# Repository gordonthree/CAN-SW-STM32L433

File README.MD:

# DC Power Distribution Module Controller
Compact controller board intended to interface with as many as four smart switch modules. Analog inputs for current and voltage sensing allow the controller to interrupt a load in place of a mechanical fuse or circuit breaker. An isolated CAN-FD interface provides expansion capability with other boards, displays and sensors.

# Control Node
* STM32L433 Microcontroller
* 3-pin terminal block for CANBUS connection with drain
* Pin-header connections for Profet Smart Switch modules
* Analog inputs for voltage and current sensing
* Jumper selected CAN terminator resistor
* LED indicator for 3.3v power
* LED indicator for status, controlled by the micro
* Bidirectional transient voltage protection diode for harsh environments
* Debugging header for UART1 serial port as well as SWLINK programming

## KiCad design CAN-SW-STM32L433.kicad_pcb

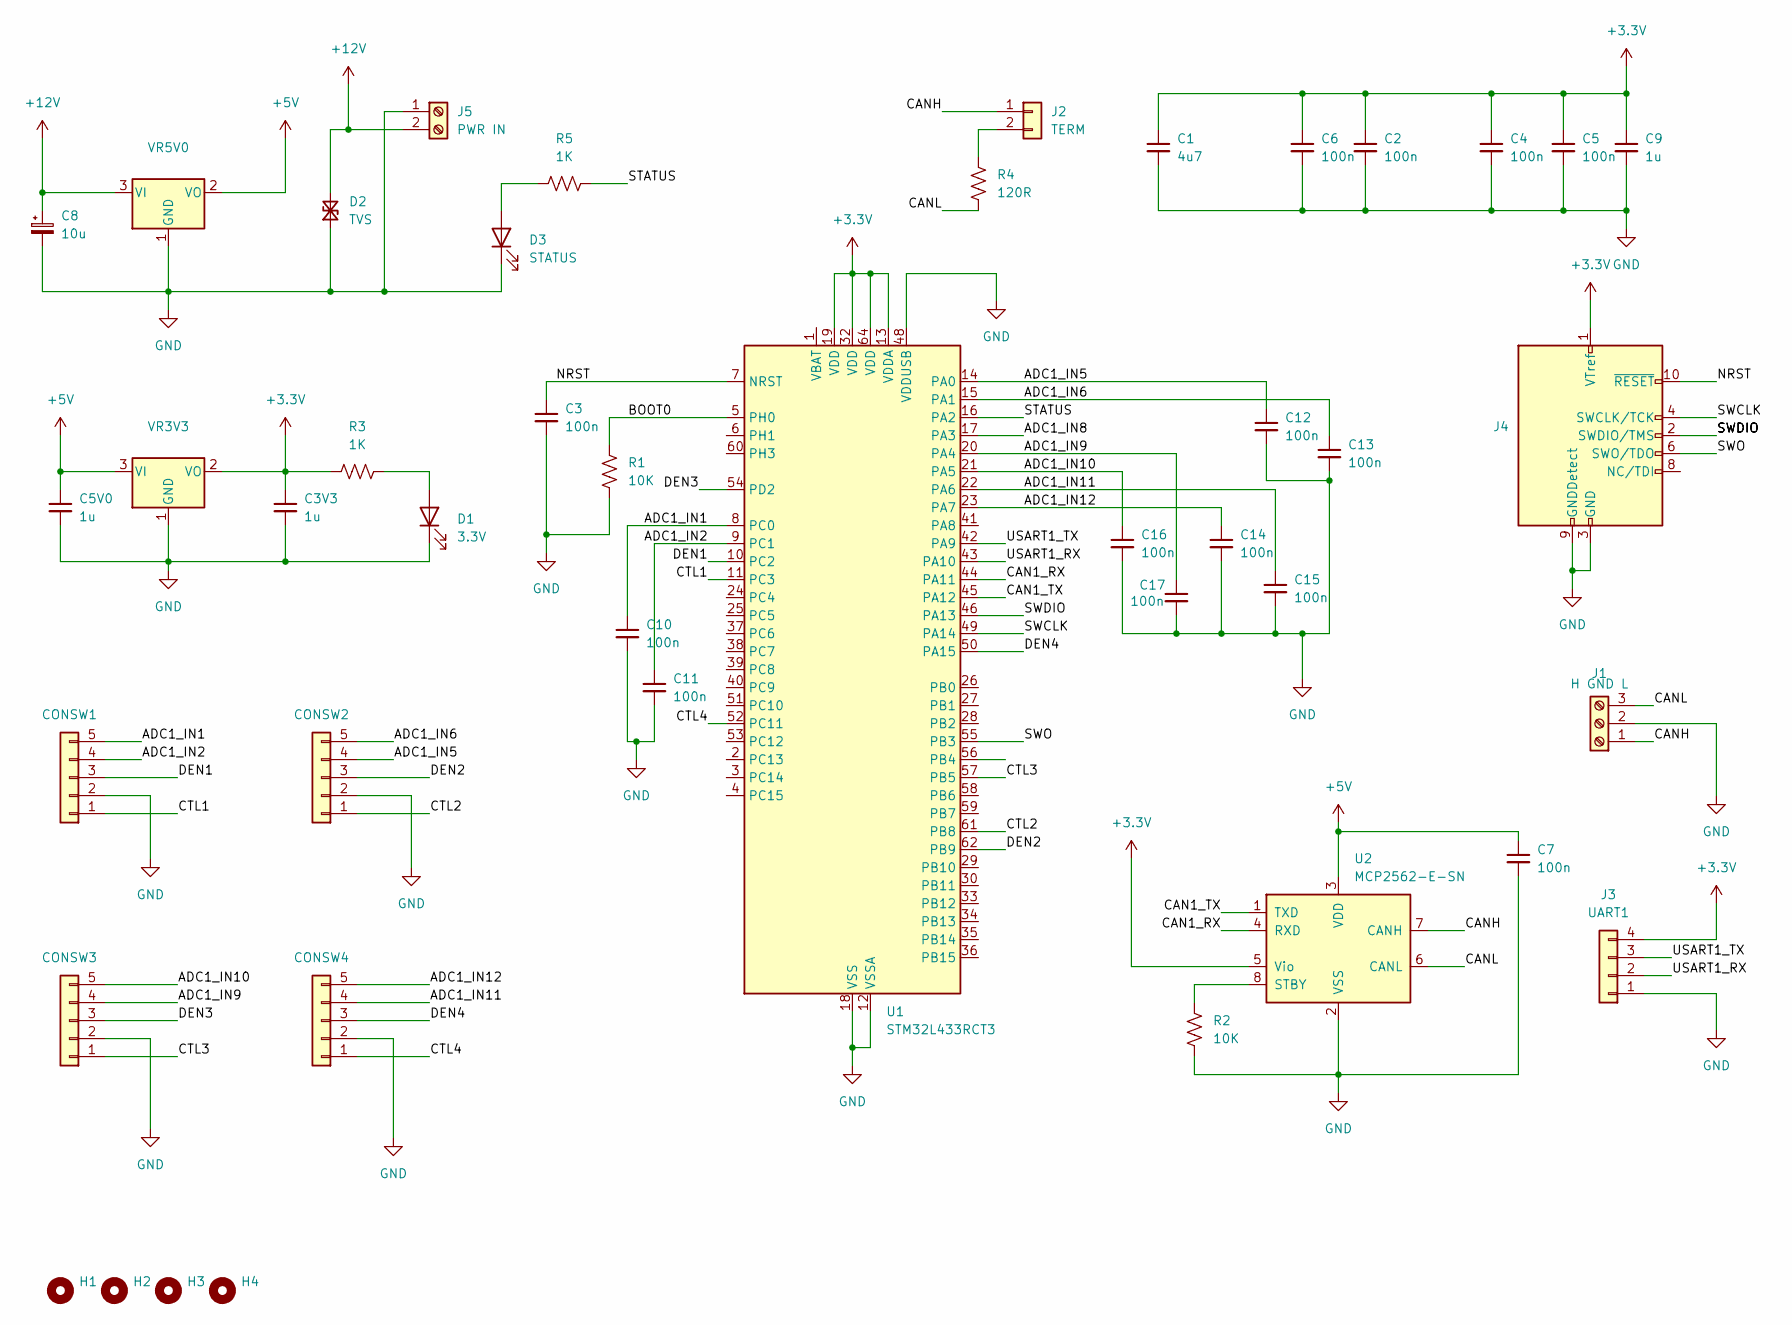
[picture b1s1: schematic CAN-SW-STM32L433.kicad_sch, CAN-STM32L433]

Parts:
C1: 4u7; C_0805_2012Metric_Pad1.18x1.45mm_HandSolder
C2, C3, C4, C5, C6, C7, C10, C11, C12, C13, C14, C15, C16, C17: 100n; C_0603_1608Metric_Pad1.08x0.95mm_HandSolder
C3V3, C5V0: 1u; C_0805_2012Metric_Pad1.18x1.45mm_HandSolder
C8: 10u; CP_Radial_D5.0mm_P2.50mm
C9: 1u; C_0603_1608Metric_Pad1.08x0.95mm_HandSolder
CONSW1, CONSW2, CONSW3, CONSW4: Conn_01x05; PinHeader_1x05_P2.54mm_Horizontal
D1: 3.3V; LED_D5.0mm_Clear
D2: TVS; D_SMA_Handsoldering
D3: STATUS; LED_D5.0mm_Clear
H1, H2, H3, H4: MountingHole; MountingHole_3.2mm_M3_DIN965
J1: H GND L; TerminalBlock_Phoenix_MKDS-1,5-3_1x03_P5.00mm_Horizontal
J2: TERM; PinHeader_1x02_P2.54mm_Vertical
J3: UART1; PinHeader_1x04_P2.54mm_Horizontal
J4: SWLINK; PinHeader_2x05_P2.54mm_Horizontal
J5: PWR IN; TerminalBlock_Phoenix_MKDS-1,5-2_1x02_P5.00mm_Horizontal
R1, R2: 10K; R_0603_1608Metric_Pad0.98x0.95mm_HandSolder
R3, R5: 1K; R_0603_1608Metric_Pad0.98x0.95mm_HandSolder
R4: 120R; R_Axial_DIN0207_L6.3mm_D2.5mm_P7.62mm_Horizontal
U1: STM32L433RCT3; LQFP-64_10x10mm_P0.5mm
U2: MCP2562-E-SN; SOIC-8_3.9x4.9mm_P1.27mm
VR3V3: TLV1117-33; SOT-223-3_TabPin2
VR5V0: TLV1117-50; SOT-223-3_TabPin2

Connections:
+3.3V: C1.1, C2.1, C3V3.1, C4.1, C5.1, C6.1, C9.1, J3.4, J4.1 (VTref), R3.1, U1.13 (VDDA), U1.19 (VDD), U1.32 (VDD), U1.64 (VDD), U2.5 (Vio), VR3V3.2 (VO)
+5V: C5V0.1, C7.1, U2.3 (VDD), VR3V3.3 (VI), VR5V0.2 (VO)
+12V: C8.1, D2.2 (A2), J5.2, VR5V0.3 (VI)
/ADC1_IN1: C10.1, CONSW1.5, U1.8 (PC0)
/ADC1_IN2: C11.1, CONSW1.4, U1.9 (PC1)
/ADC1_IN5: C12.1, CONSW2.4, U1.14 (PA0)
/ADC1_IN6: C13.1, CONSW2.5, U1.15 (PA1)
/ADC1_IN8: U1.17 (PA3)
/ADC1_IN9: C17.1, CONSW3.4, U1.20 (PA4)
/ADC1_IN10: C16.1, CONSW3.5, U1.21 (PA5)
/ADC1_IN11: C15.1, CONSW4.4, U1.22 (PA6)
/ADC1_IN12: C14.1, CONSW4.5, U1.23 (PA7)
/BOOT0: R1.1, U1.5 (PH0)
/CAN1_RX: U1.44 (PA11), U2.4 (RXD)
/CAN1_TX: U1.45 (PA12), U2.1 (TXD)
/CANH: J1.1, J2.1, U2.7 (CANH)
/CANL: J1.3, R4.2, U2.6 (CANL)
/CTL1: CONSW1.1, U1.11 (PC3)
/CTL2: CONSW2.1, U1.61 (PB8)
/CTL3: CONSW3.1, U1.57 (PB5)
/CTL4: CONSW4.1, U1.52 (PC11)
/DEN1: CONSW1.3, U1.10 (PC2)
/DEN2: CONSW2.3, U1.62 (PB9)
/DEN3: CONSW3.3, U1.54 (PD2)
/DEN4: CONSW4.3, U1.50 (PA15)
/NRST: C3.1, J4.10 (~RESET), U1.7 (NRST)
/STATUS: R5.2, U1.16 (PA2)
/SWCLK: J4.4 (SWCLK/TCK), U1.49 (PA14)
/SWDIO: J4.2 (SWDIO/TMS), U1.46 (PA13)
/SWO: J4.6 (SWO/TDO), U1.55 (PB3)
/USART1_RX: J3.2, U1.43 (PA10)
/USART1_TX: J3.3, U1.42 (PA9)
GND: C1.2, C2.2, C3.2, C3V3.2, C4.2, C5.2, C5V0.2, C6.2, C7.2, C8.2, C9.2, C10.2, C11.2, C12.2, C13.2, C14.2, C15.2, C16.2, C17.2, CONSW1.2, CONSW2.2, CONSW3.2, CONSW4.2, D1.1 (K), D2.1 (A1), D3.1 (K), J1.2, J3.1, J4.3 (GND), J4.5 (GND), J4.9 (GNDDetect), J5.1, R1.2, R2.2, U1.12 (VSSA), U1.18 (VSS), U1.31 (VSS), U1.47 (VSS), U1.48 (VDDUSB), U1.63 (VSS), U2.2 (VSS), VR3V3.1 (GND), VR5V0.1 (GND)
unnamed: D1.2 (A), R3.2
unnamed: D3.2 (A), R5.1
unnamed: J2.2, R4.1
unnamed: R2.1, U2.8 (STBY)

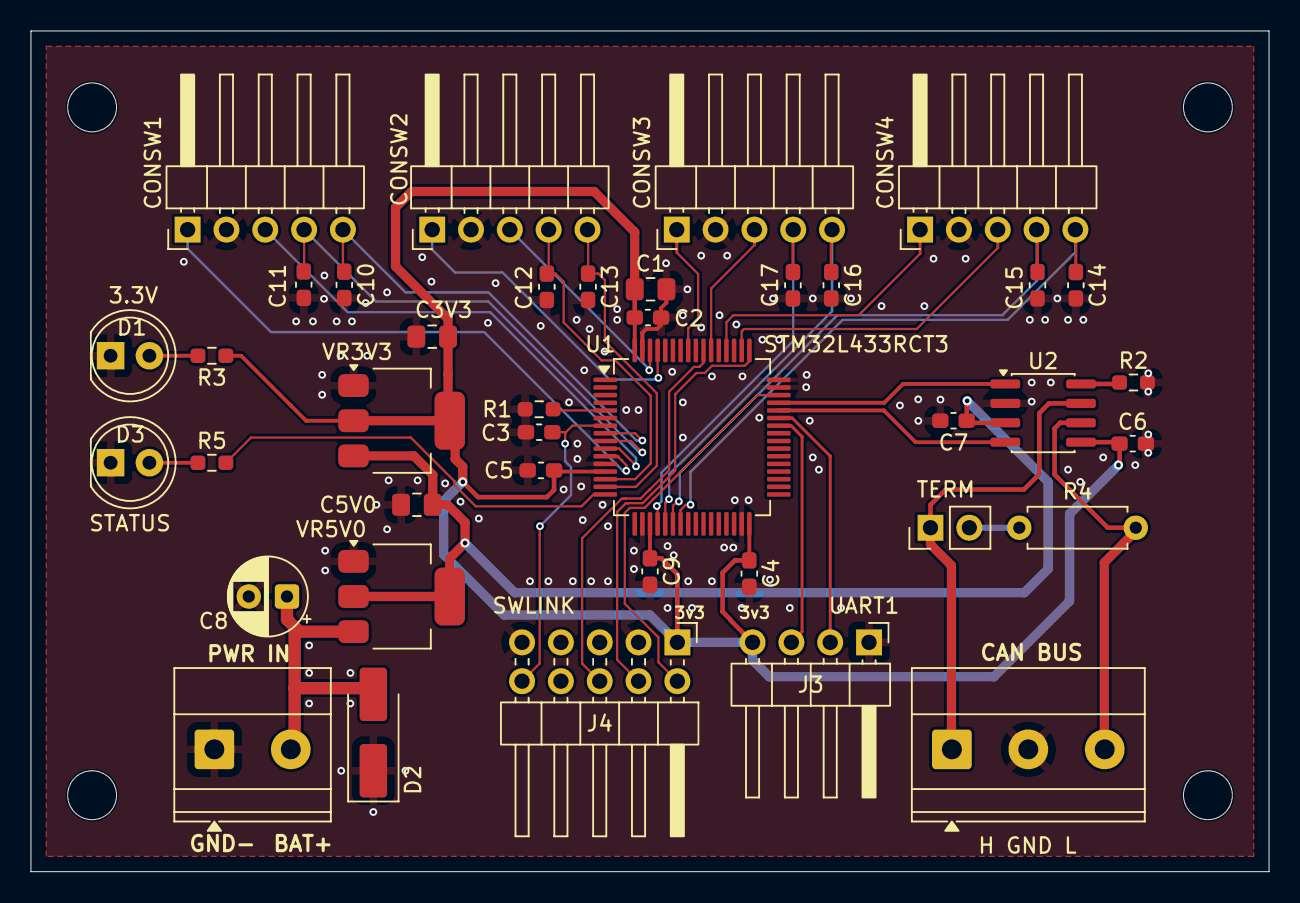
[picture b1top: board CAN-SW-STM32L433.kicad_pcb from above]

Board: 2 copper layers, 81.0 x 55.0 mm, 44 parts (0 on the bottom side), 36 nets.

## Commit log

2026-01-12 dive in with kicad
2026-01-12 created readme
2026-01-13 still adding parts, working on basic layout
2026-01-14 almost done adding parts, working more on layout
2026-01-14 more progress on the layout, fixed connector sizes for uart and swlink
2026-01-14 routing getting tricky with just two layers
2026-01-15 layout mostly complete, working on DRC
2026-01-15 layout and drc complete, fix some silkscreen issues
2026-01-15 add gerber export folder to ignore list
2026-01-15 moved power and can connectors, fixed some trace routing
2026-01-15 silkscreen tweaks
2026-01-17 added status led and tvs diode
2026-01-17 fix TVS package size, do some layout tweaks
2026-01-17 add 3d board rendering
2026-01-17 add desktop.ini to ignore
2026-01-17 update readme with more info and board rendering
2026-01-17 add more info
2026-01-18 layout tweak

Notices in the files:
CAN-SW-STM32L433.kicad_pcb:
(C) 2026 G MCLELLAN
